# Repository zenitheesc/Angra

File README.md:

<h1 align="center" style="color:white; background-color:black">Angra</h1>
<h4 align="center">Power bank to power different systems in stratospheric probes</h4>

<p align="center">

</p>

<p align="center">
    <a href="#environment-and-tools">Environment and Tools</a> •
    <a href="#board">Board</a>
</p>

## Environment and tools

This system was designed using Eagle v.9.4.2

## Board

It supplies power to up to 5 systems with the voltage of its own batteries and 1 with 5V, in addition to ensuring the health of the batteries, solar charging and wireless monitoring of the status.

---

<p align="center">

</p>
<p align = "center">
<a href="zenith.eesc@gmail.com">zenith.eesc@gmail.com</a>
</p>

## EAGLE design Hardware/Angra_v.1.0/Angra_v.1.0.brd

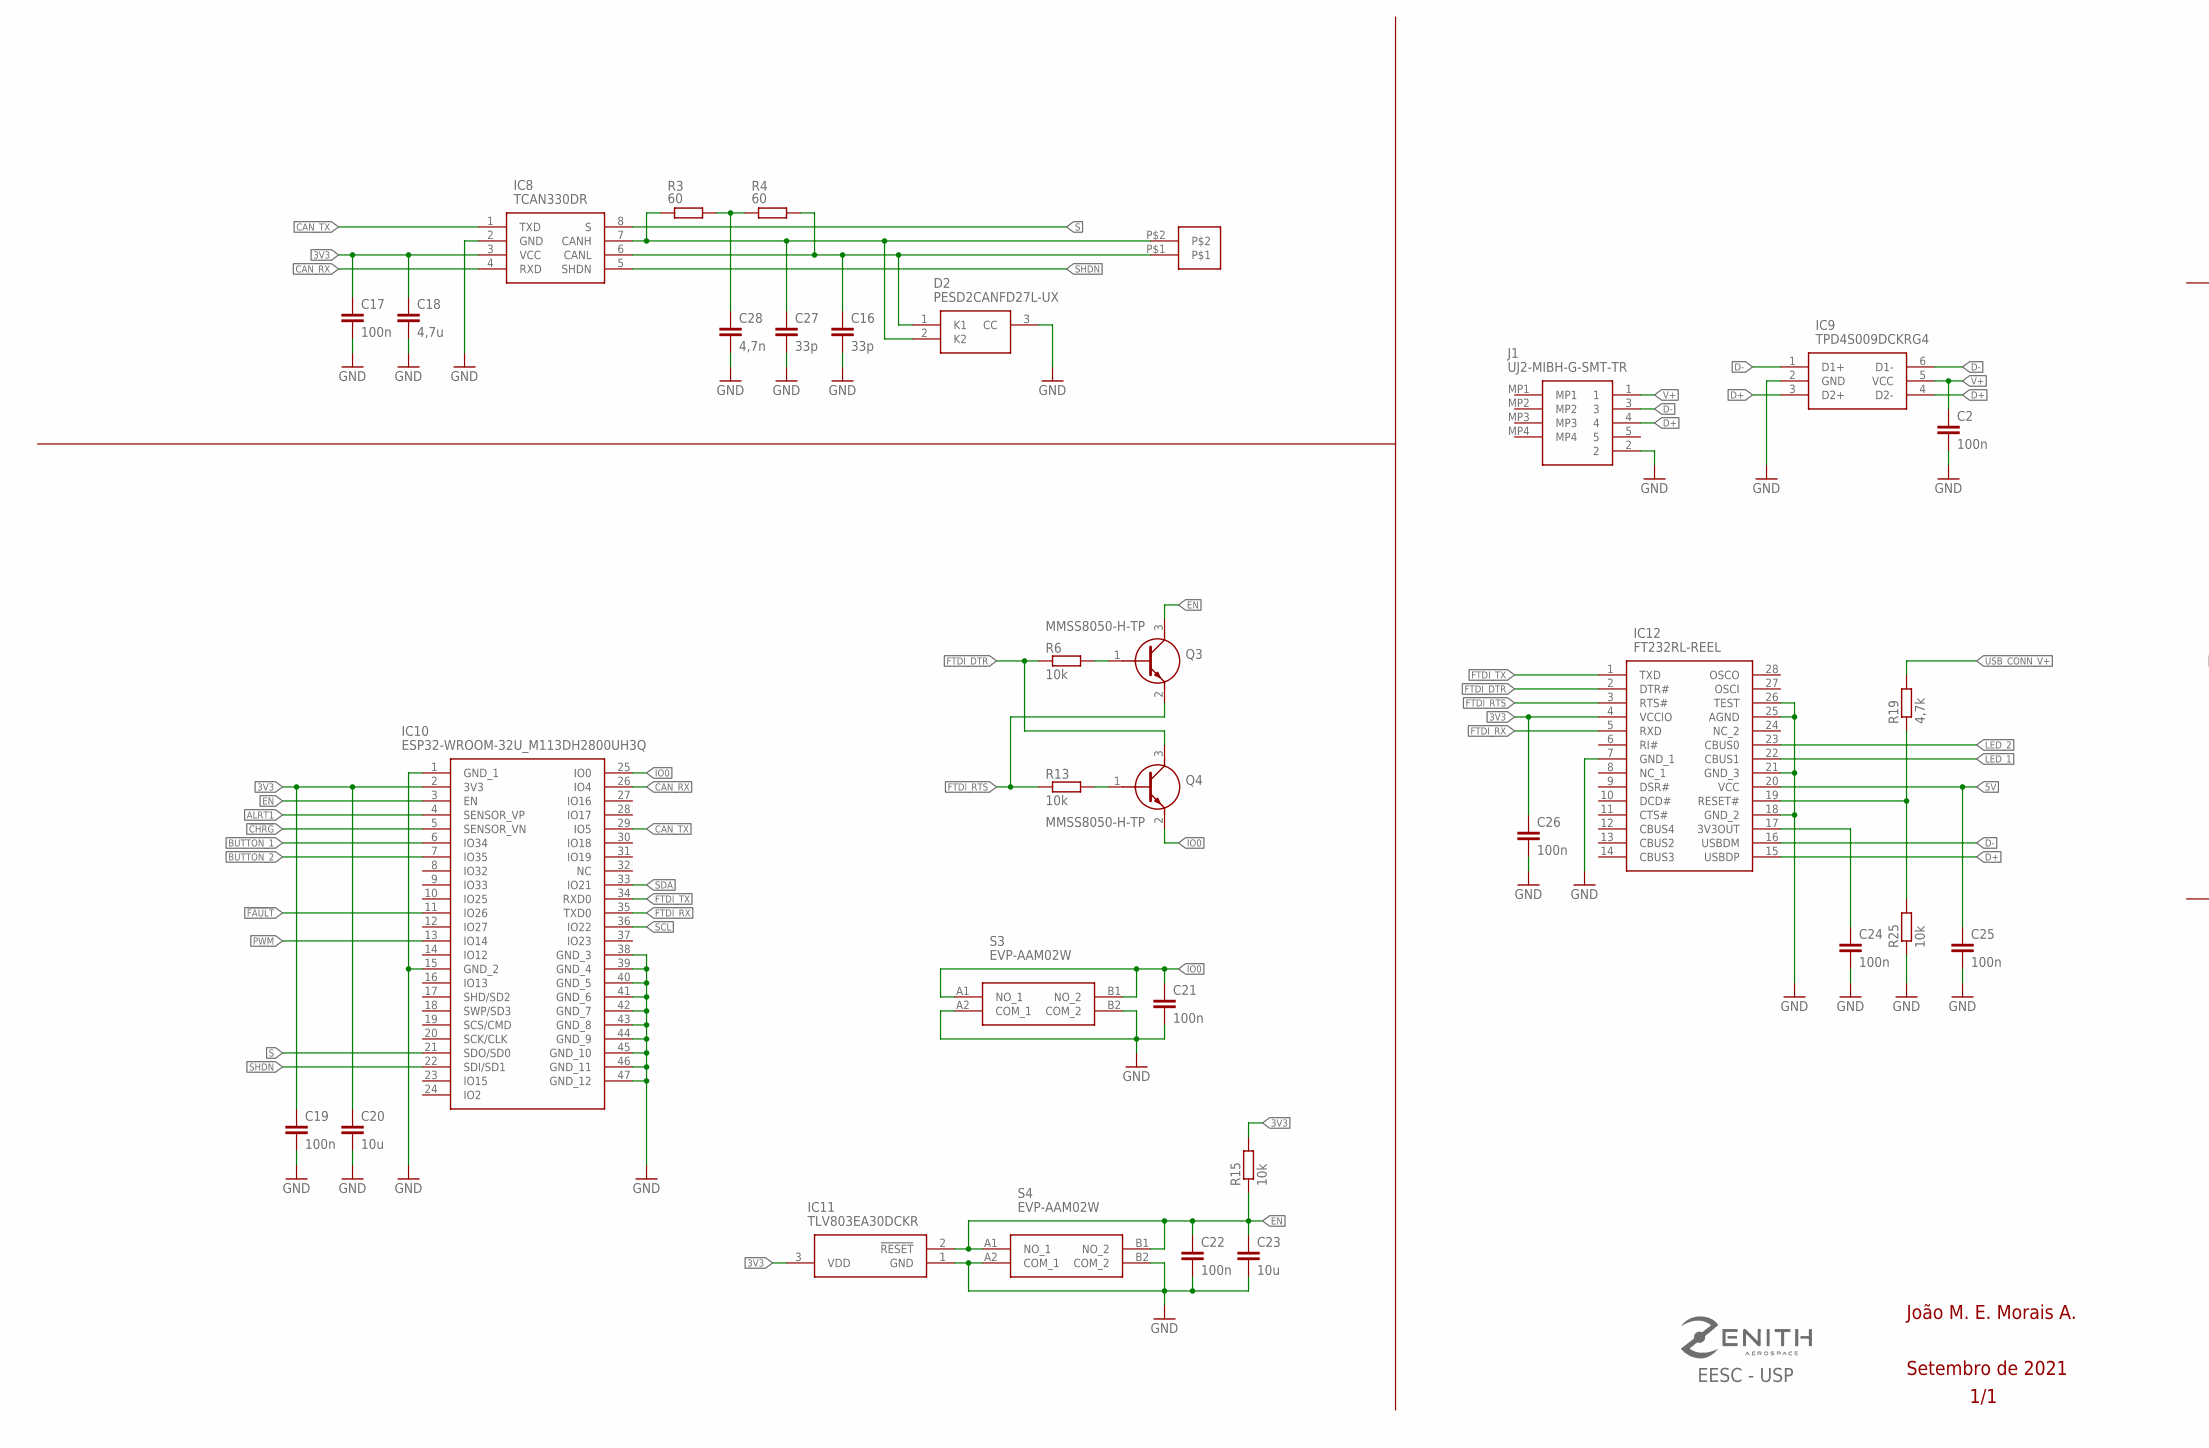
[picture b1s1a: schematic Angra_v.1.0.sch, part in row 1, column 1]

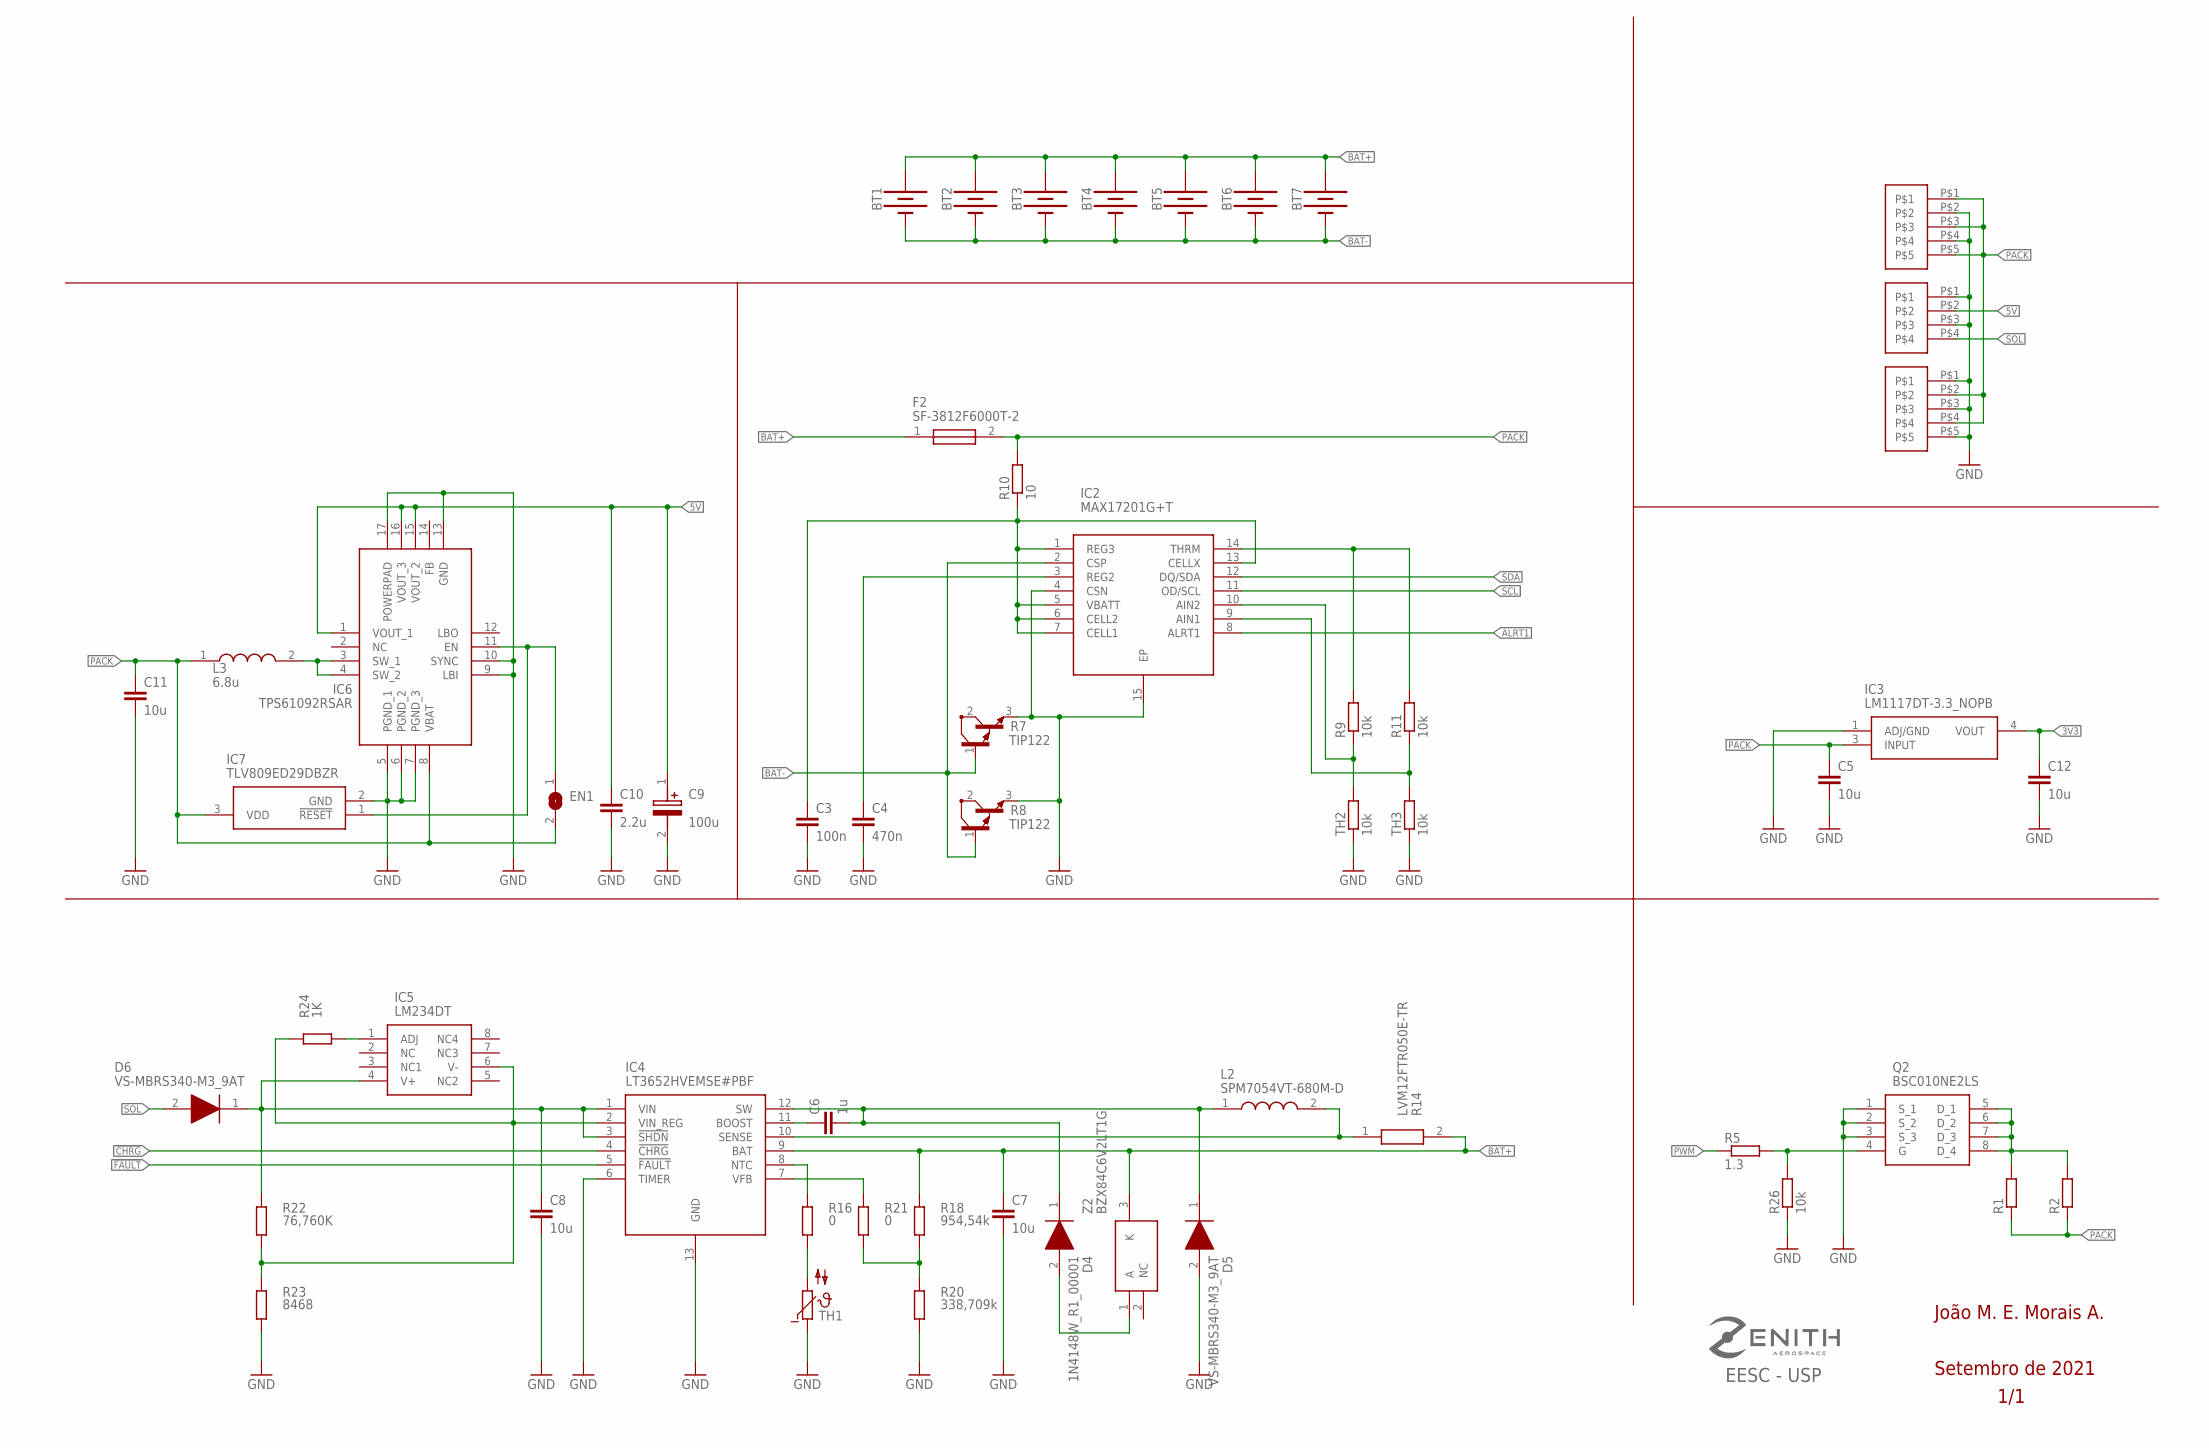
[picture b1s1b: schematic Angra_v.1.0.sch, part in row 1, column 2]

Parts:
BT1, BT2, BT3, BT4, BT5, BT6, BT7: BATTERY-18650; BATTERY_18650-HOLDER
C2, C3, C17, C19, C21, C22, C24, C25, C26: 100n; C0805
C4: 470n; C0805
C5, C7, C8, C12, C20, C23: 10u; C0805
C6: 1u; C0805
C9: 100u; CAPPM3528X210N
C10: 2.2u; C1206
C11: 10u; C1206
C16, C27: 33p; C0805
C18: 4,7u; C0805
C28: 4,7n; C0805
D2: PESD2CANFD27L-UX; SOT65P210X110-3N
D4: 1N4148W_R1_00001; SOD3816X135N
D5, D6: VS-MBRS340-M3_9AT; DIOM7959X262N
EN1: SOLDERJUMPERREFLOW_NOPASTE; SOLDERJUMPER_REFLOW_NOPASTE
F2: SF-3812F6000T-2; FUSC10131X330N
IC2: MAX17201G+T; SON40P300X300X80-15N
IC3: LM1117DT-3.3_NOPB; TO228P991X238-3N
IC4: LT3652HVEMSE#PBF; SOP65P490X110-13N
IC5: LM234DT; SOIC127P600X175-8N@1
IC6: TPS61092RSAR; QFN65P400X400X100-17N
IC7: TLV809ED29DBZR; SOT95P237X112-3N
IC8: TCAN330DR; SOIC127P600X175-8N
IC9: TPD4S009DCKRG4; SOT65P210X110-6N
IC10: ESP32-WROOM-32U_M113DH2800UH3Q; ESP32WROOM32UM113DH2800UH3Q0
IC11: TLV803EA30DCKR; SOT65P210X110-3N@1
IC12: FT232RL-REEL; SOP65P778X200-28N
J1: UJ2-MIBH-G-SMT-TR; UJ2MIBHGSMTTR
L2: SPM7054VT-680M-D; SPM7054VT
L3: 6.8u; INDPM4040X210N
Q2: BSC010NE2LS; PG-TDSON-8
Q3, Q4: MMSS8050-H-TP; SI2305TP
R1, R2: R-EU_0207/7; 0207/7
R3, R4: 60; R0805
R5: 1.3; R0805
R6, R9, R11, R13, R15, R25, R26: 10k; R0805
R7, R8: TIP122; TO220
R10: 10; R0805
R14: LVM12FTR050E-TR; RESC3016X70N
R16, R21: 0; R0805
R18: 954,54k; R0805
R19: 4,7k; R0805
R20: 338,709k; R0805
R22: 76,760K; R0805
R23: 8468; R0805
R24: 1K; R0805
S3, S4: EVP-AAM02W; EVPAAM02W
TH1: NTC640; P640
TH2, TH3: 10k; 0207/7
U$1: S02B-XASS-1
U$2, U$3: S05B-XASS-1
U$4: S04B-XASS-1
Z2: BZX84C6V2LT1G; SOT96P237X111-3N

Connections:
3V3: C12.1, C17.1, C18.1, C19.1, C20.1, C26.1, IC3.4 (VOUT), IC8.3 (VCC), IC10.2 (3V3), IC11.3 (VDD), IC12.4 (VCCIO), R15.2
5V: C9.1 (+), C10.1, C25.1, IC6.1 (VOUT_1), IC6.15 (VOUT_2), IC6.16 (VOUT_3), IC12.20 (VCC), U$4.P$2
!CHRG: IC4.4 (!CHRG), IC10.5 (SENSOR_VN)
!FAULT: IC4.5 (!FAULT), IC10.11 (IO26)
ALRT1: IC2.8 (ALRT1), IC10.4 (SENSOR_VP)
BAT+: BT1.PWR@1 (+), BT2.PWR@1 (+), BT3.PWR@1 (+), BT4.PWR@1 (+), BT5.PWR@1 (+), BT6.PWR@1 (+), BT7.PWR@1 (+), C7.1, F2.1, IC4.9 (BAT), R14.2, R18.1, Z2.3 (K)
BAT-: BT1.GND@1 (-), BT2.GND@1 (-), BT3.GND@1 (-), BT4.GND@1 (-), BT5.GND@1 (-), BT6.GND@1 (-), BT7.GND@1 (-), IC2.2 (CSP), R7.1 (B), R8.1 (B)
BUTTON_1: IC10.6 (IO34)
BUTTON_2: IC10.7 (IO35)
CANH: C27.1, D2.2 (K2), IC8.7 (CANH), R3.2, U$1.P$2
CANL: C16.1, D2.1 (K1), IC8.6 (CANL), R4.1, U$1.P$1
CAN_RX: IC8.4 (RXD), IC10.26 (IO4)
CAN_TX: IC8.1 (TXD), IC10.29 (IO5)
D+: IC9.3 (D2+), IC9.4 (D2-), IC12.15 (USBDP), J1.4
D-: IC9.1 (D1+), IC9.6 (D1-), IC12.16 (USBDM), J1.3
EN: C22.1, C23.1, IC10.3 (EN), IC11.2 (!RESET), Q3.3 (C), R15.1, S4.A1 (NO_1), S4.B1 (NO_2)
FTDI_DTR: IC12.2 (DTR#), Q4.3 (C), R6.1
FTDI_RTS: IC12.3 (RTS#), Q3.2 (E), R13.1
FTDI_RX: IC10.35 (TXD0), IC12.5 (RXD)
FTDI_TX: IC10.34 (RXD0), IC12.1 (TXD)
GND: C2.2, C3.2, C4.2, C5.2, C7.2, C8.2, C9.2 (-), C10.2, C11.2, C12.2, C16.2, C17.2, C18.2, C19.2, C20.2, C21.2, C22.2, C23.2, C24.2, C25.2, C26.2, C27.2, C28.2, D2.3 (CC), D5.2 (A), IC2.4 (CSN), IC2.15 (EP), IC3.1 (ADJ/GND), IC4.6 (TIMER), IC4.13 (GND), IC6.5 (PGND_1), IC6.6 (PGND_2), IC6.7 (PGND_3), IC6.9 (LBI), IC6.10 (SYNC), IC6.13 (GND), IC6.17 (POWERPAD), IC7.2 (GND), IC8.2 (GND), IC9.2 (GND), IC10.1 (GND_1), IC10.15 (GND_2), IC10.38 (GND_3), IC10.39 (GND_4), IC10.40 (GND_5), IC10.41 (GND_6), IC10.42 (GND_7), IC10.43 (GND_8), IC10.44 (GND_9), IC10.45 (GND_10), IC10.46 (GND_11), IC10.47 (GND_12), IC11.1 (GND), IC12.7 (GND_1), IC12.18 (GND_2), IC12.21 (GND_3), IC12.25 (AGND), IC12.26 (TEST), J1.2, Q2.1 (S_1), Q2.2 (S_2), Q2.3 (S_3), R7.3 (E), R8.3 (E), R20.2, R23.2, R25.1, R26.1, S3.A2 (COM_1), S3.B2 (COM_2), S4.A2 (COM_1), S4.B2 (COM_2), TH1.1, TH2.1, TH3.1, U$2.P$2, U$2.P$4, U$3.P$1, U$3.P$3, U$3.P$5, U$4.P$1, U$4.P$3
IO0: C21.1, IC10.25 (IO0), Q4.2 (E), S3.A1 (NO_1), S3.B1 (NO_2)
LED_1: IC12.22 (CBUS1)
LED_2: IC12.23 (CBUS0)
unnamed: C28.1, R3.1, R4.2
unnamed: IC6.3 (SW_1), IC6.4 (SW_2), L3.2
unnamed: EN1.1, IC6.11 (EN), IC7.1 (!RESET)
unnamed: Q2.4 (G), R5.2, R26.2
unnamed: Q4.1 (B), R13.2
unnamed: Q3.1 (B), R6.2
unnamed: C3.1, IC2.1 (REG3), IC2.5 (VBATT), IC2.6 (CELL2), IC2.7 (CELL1), IC2.13 (CELLX), R10.1
unnamed: C4.1, IC2.3 (REG2)
unnamed: IC2.14 (THRM), R9.2, R11.2
unnamed: IC2.10 (AIN2), R9.1, TH2.2
unnamed: IC2.9 (AIN1), R11.1, TH3.2
unnamed: IC12.19 (RESET#), R19.1, R25.2
unnamed: C24.1, IC12.17 (3V3OUT)
unnamed: IC4.10 (SENSE), L2.2, R14.1
unnamed: IC4.8 (NTC), R16.1
unnamed: R16.2, TH1.2
unnamed: C6.2, D4.1 (K), D5.1 (K), IC4.12 (SW), L2.1
unnamed: IC4.7 (VFB), R21.1
unnamed: R18.2, R20.1, R21.2
unnamed: C6.1, IC4.11 (BOOST)
unnamed: C8.1, D6.1 (K), IC4.1 (VIN), IC4.3 (!SHDN), IC5.4 (V+), R22.1
unnamed: IC4.2 (VIN_REG), IC5.6 (V-), R22.2, R23.1, R24.1
unnamed: IC5.1 (ADJ), R24.2
unnamed: D4.2 (A), Z2.1 (A)
PACK: C5.1, C11.1, EN1.2, F2.2, IC3.3 (INPUT), IC6.8 (VBAT), IC7.3 (VDD), L3.1, R1.1, R2.1, R10.2, U$2.P$1, U$2.P$3, U$2.P$5, U$3.P$2, U$3.P$4
PWM: IC10.13 (IO14), R5.1
RL: Q2.5 (D_1), Q2.6 (D_2), Q2.7 (D_3), Q2.8 (D_4), R1.2, R2.2
S: IC8.8 (S), IC10.21 (SDO/SD0)
SCL: IC2.11 (OD/SCL), IC10.36 (IO22)
SDA: IC2.12 (DQ/SDA), IC10.33 (IO21)
SHDN: IC8.5 (SHDN), IC10.22 (SDI/SD1)
SOL: D6.2 (A), U$4.P$4
USB_CONN_V+: R19.2
V+: C2.1, IC9.5 (VCC), J1.1

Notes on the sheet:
C:/Users/marcu/Desktop/Ensino Superior/Graduação - Eng Elétrica/Zenith/zenith-v2.bmp
EESC - USP
Setembro de 2021
1/1
João M. E. Morais A.

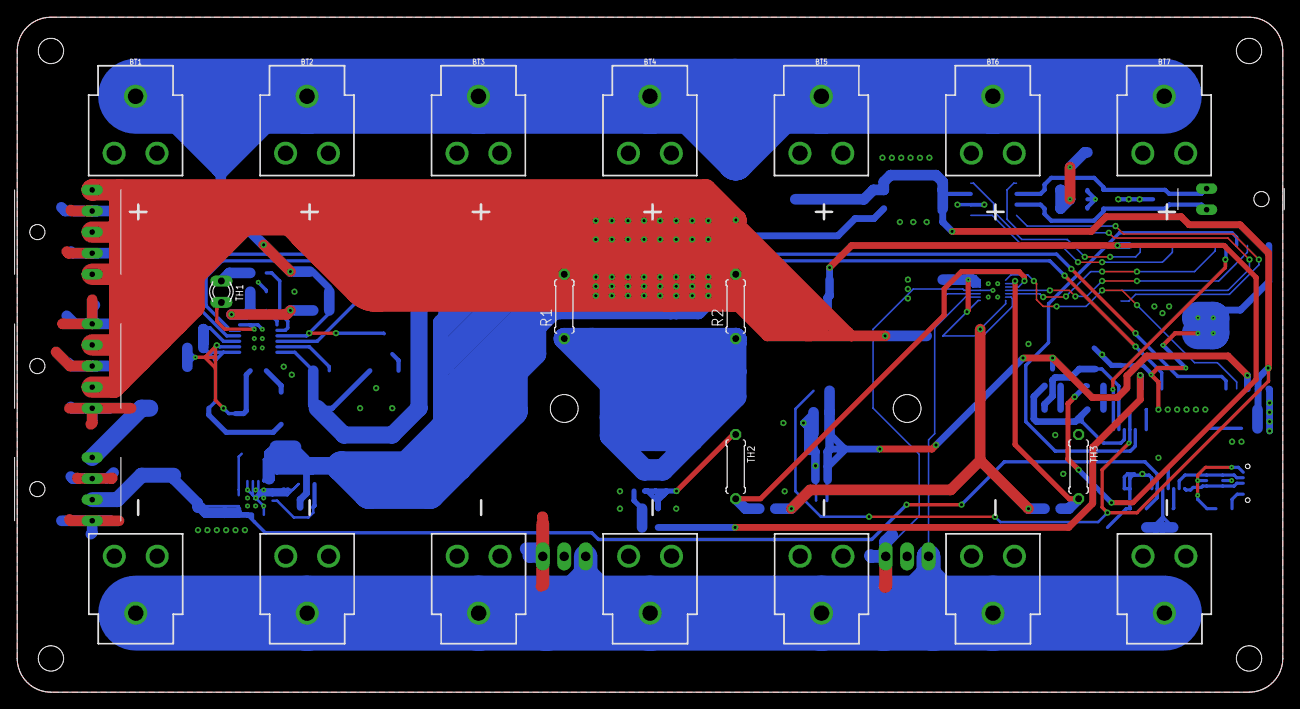
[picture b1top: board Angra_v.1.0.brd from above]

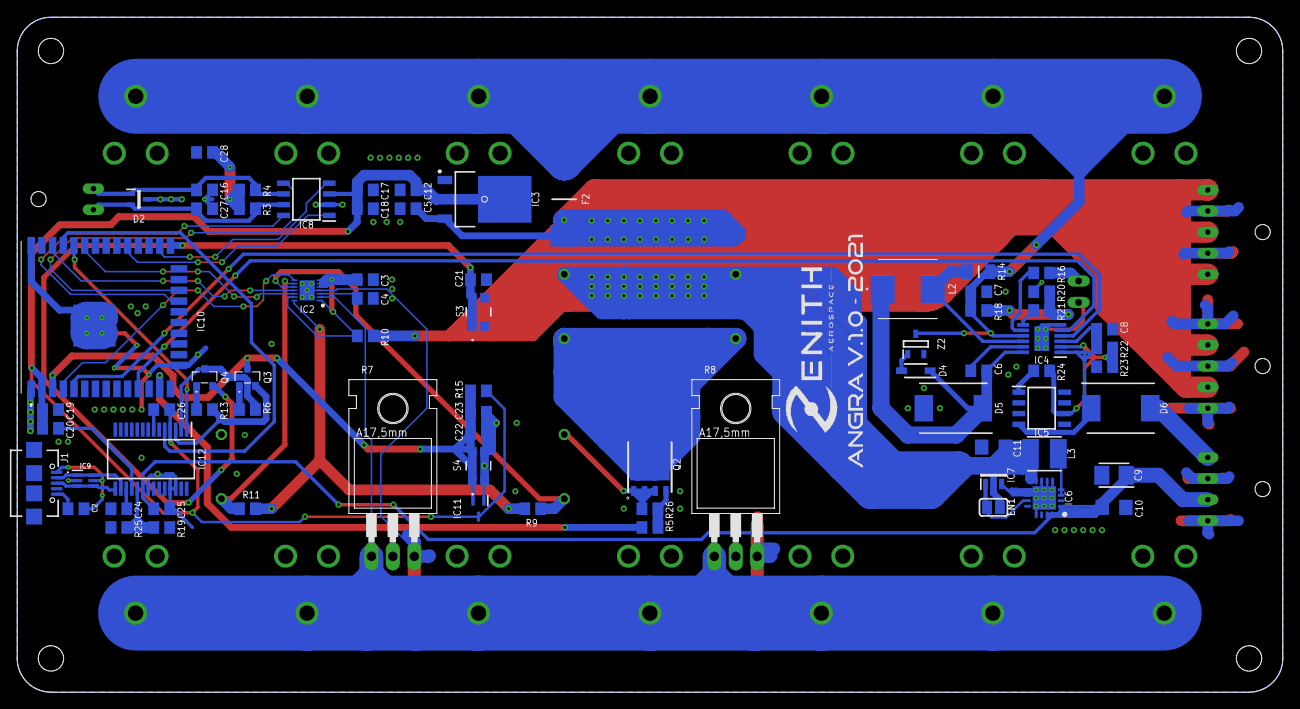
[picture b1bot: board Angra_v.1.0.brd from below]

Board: 2 copper layers, 150.0 x 80.0 mm, 88 parts (72 on the bottom side), 53 nets.

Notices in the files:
parts and their libraries:
SparkFun-Batteries: Licensing: Creative Commons ShareAlike 4.0 International - https://creativecommons.org/licenses/by-sa/4.0
